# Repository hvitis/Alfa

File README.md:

[English](README.en.md) · **Polski**

# α Alfa

**Małe radio. Wielka wyobraźnia.**

Pastelowa chmurka, sześć przycisków arcade i 32 polskie litery do odkrycia. Alfa odtwarza muzykę i lekcje liter bez sieci.
Wydrukuj obudowę w swoich kolorach, zamontuj elektronikę i stwórz własne radio.

[Prezentacja w przeglądarce](https://hvitis.github.io/Alfa/) · [Najnowszy pakiet](https://github.com/hvitis/Alfa/releases/latest) · [Instrukcja sprzętu](docs/hardware-guide.md) · [Dokumentacja](docs/README.md)

## Zajrzyj do środka

| Połączenia układu | Wnętrze obudowy od tyłu | Widok rentgenowski elementów |
| --- | --- | --- |
|  |  |  |
| [Interaktywny schemat połączeń](https://hvitis.github.io/Alfa/#hardware) | [Wnętrze i montaż chmurki](design/cloud-radio/README.md) | [Pliki do druku chmurki](design/cloud-radio/README.md) |

**Odkryj warsztat:** [3DPrint](https://hvitis.github.io/Alfa/#3dprint) · [Sklejka](https://hvitis.github.io/Alfa/#plywood) · [Elektronika](https://hvitis.github.io/Alfa/#hardware) · [Oprogramowanie](https://hvitis.github.io/Alfa/#software)

**[Raspi 3 PCB — otwórz interaktywny model shielda](https://hvitis.github.io/Alfa/pcb/)** · [Projekt i instrukcja wykonania](design/pi3-shield/README.md).
Prototyp 65 × 56 mm mieści ADC, wzmacniacz i dzielnik bez osobnych modułów. Próby na sprzęcie pozostają do wykonania.

<details open>
<summary>Zobacz warsztat i schemat oprogramowania</summary>

</details>

Folder [CAD](design/) zawiera źródła obudów. Ilustrowany PDF dokumentu ADR jest w zakładce **Software → Design**.

## Specyfikacja

<!-- specifications:start -->
| Specification | Value |
| --- | --- |
| Code and documentation license | MIT |
| Runtime | Python 3.11+ |
| Validation toolchain | Python 3.12, Node.js 22, Chromium |
| Active controller | Raspberry Pi 3, Raspberry Pi OS Bookworm or newer |
| Display | ST7789, 240 × 320, SPI |
| Audio | MAX98357A, I²S, 48 kHz stereo PCM |
| Button input | Five-button keypad, ADS1115 or ADS1015, I²C |
| Divider | 2 × 10 kΩ |
| Backlight | BCM GPIO24 |
| Polish alphabet | 32 letters |
| Initial volume / cap | 20% / 50% |
| Static showcase | HTML, CSS, JavaScript; no backend |
<!-- specifications:end -->

Tabela używa tych samych nazw co wersja angielska, aby automatycznie wykrywać różnice między dokumentami.

## Funkcje

- <!-- feature:offline-player --> **Odtwarzacz bez sieci:** Pięć przycisków służy do zmiany obrazów, odtwarzania nagrań i regulacji głośności.
- <!-- feature:letter-lessons --> **Nauka liter:** Animacja rysuje 32 polskie litery, kreska po kresce. Istniejące grafiki postaci mają osobne informacje o prawach.
- <!-- feature:hardware-simulation --> **Symulacja sprzętu:** Komputer zapisuje podgląd ekranu bez urządzeń GPIO, SPI i I²C.
- <!-- feature:static-showcase --> **Prezentacja statyczna:** Zakładki Plywood, 3DPrint, Hardware i Software zawierają modele 3D, połączenia kontrolerów, ilustrowany PDF ADR i diagram Mermaid.
- <!-- feature:verified-distribution --> **Sprawdzany pakiet:** Pakiet zawiera neutralny obraz demonstracyjny, sumy kontrolne, raporty walidacji i zestawienie elektroniki.
- <!-- feature:enclosure-research --> **Projekty obudów:** Prezentacja obejmuje drukowaną chmurkę i oba projekty ze sklejki. Chmurka ma 206 × 211 × 72 mm, boczną pokrywę baterii, baterię i Pi równoległe do tyłu oraz przyciski zamocowane w przedniej skorupie. Otwory głośnika mają kształt chmur. Pliki STL, 3MF, BREP i kupony pasowania są dołączone; skorupa z brimem 2 mm mieści się w polu Endera 220 × 220 mm. [Opis konstrukcji](design/cloud-radio/README.md) · [30 usprawnień](design/cloud-radio/IMPROVEMENTS.md).

## Szybki start

Użyj Pythona 3.11 lub nowszego. Zainstaluj FFmpeg do konwersji dźwięku.

```bash
python3 -m venv .venv
source .venv/bin/activate
python -m pip install -r requirements/base.txt
python -m app --simulate player --once --no-audio
```

Symulator zapisuje `.state/preview/current.png`. Repozytorium korzysta z istniejących przygotowanych multimediów.
Aplikacja, usługa Pi, ekran startowy i podgląd w przeglądarce używają jednego [config.json](config.json), z wyborem liter w `lesson.letters`.
Plik [installation.md](docs/installation.md) opisuje instalację lokalną i na Pi, a [configuration.md](docs/configuration.md) opisuje ustawienia.
Pakiet wydania zawiera neutralny obraz demonstracyjny.
Połączenia, kalibrację przycisków, sprawdzanie głośnika i instalację usługi opisuje [instrukcja sprzętu](docs/hardware-guide.md).

Po zamontowaniu lub obróceniu przycisków w obudowie uruchom na Pi `make mapping`.
Przypisz kolejno LEWO, PRAWO, GÓRĘ, DÓŁ i ŚRODEK zgodnie z instrukcjami. Polecenie przywraca wcześniej uruchomioną usługę.

Aby wyświetlić obraz na Pi 3 przed uruchomieniem Linuksa, użyj [instrukcji ekranu startowego firmware](docs/early-boot-splash.md).
Opisuje zgodny firmware, `make firmware-splash-install`, kopie zapasowe i usuwanie zmian.

Zainstaluj narzędzia programistyczne i uruchom lokalną prezentację:

```bash
make install
make check
make serve
```

Otwórz lokalny adres wypisany przez `make serve`. System wybiera wolny port; opcjonalnie ustaw `make serve SERVE_PORT=53173`. Testy przeglądarki wymagają Node.js 22.
Plik [build-guide.md](docs/build-guide.md) opisuje wymagania Linuksa i środowisko.

## Automatyczna walidacja

`make check` sprawdza konfigurację, testy Pythona, składnię JavaScript, dane przeglądarki 3D i zgodność dokumentacji dwujęzycznej.
CI eksportuje prezentację i sprawdza ją w Chromium, w katalogu głównym oraz podkatalogu repozytorium, na ekranie komputera i telefonu.
Testy obejmują oba modele ze sklejki, drukowaną obudowę chmurki, połączenia obu kontrolerów, ADR, diagram Mermaid i lokalne zasoby.
`make build` uruchamia również symulator z pakietu i sprawdza zawartość archiwum oraz sumy SHA-256.

Połączenia fizyczne, głośność akustyczna, dopasowanie obudowy i prawa do multimediów wymagają osobnego przeglądu.
Automatyzacja oprogramowania nie potwierdza tych właściwości.

## Budowanie i publikacja

```bash
make smoke
make build
```

Pakiet powstaje jako `output/Alfa-Build-Kit.zip`. Raporty trafiają do `output/reports/`.
Pakiet zawiera aplikację Python, instrukcję połączeń, neutralny obraz i prezentację statyczną z siatkami modeli 3D.
Nie zawiera grafik postaci, nagrań ani starszej przeglądarki. Strona zawiera pliki chmurki do druku. Źródła strony i generator są w [web/](web/README.md).
Przeczytaj [zawartość wydania](docs/release-contents.md), [opis automatyzacji](docs/pipeline.md) i [kroki publikacji](docs/publishing.md).

CI sprawdza pull requesty. GitHub Pages wdraża stronę po poprawnych testach na `main`.
Wydanie wymaga tagu SemVer wskazującego rzeczywisty commit z gałęzi `main`.

## Współpraca i licencje

Plik [contributing.md](docs/contributing.md) opisuje pracę nad kodem.
Problemy bezpieczeństwa zgłaszaj zgodnie z [SECURITY.md](SECURITY.md).
[Licencja MIT](LICENSE) obejmuje oryginalny kod i dokumentację techniczną.
Plik [Informacje o zasobach i zależnościach](docs/third-party-notices.md) opisuje wyłączenia dotyczące zasobów i informacje o zależnościach.

Obudowa jest prototypem do sprawdzenia dopasowania. Próby fizyczne języków ustalających, zatrzasków, upadków i temperatury są nadal wymagane.
Grafiki postaci i nagrania wymagają osobnego przeglądu praw przed publikacją. Zobacz [listę czynności przed publikacją](docs/publishing.md).
Obrazy w README i karty społecznościowe są oryginalnymi renderami CAD.

Aby odtworzyć obrazy, uruchom `make dev`, a potem `npm run render:assets`. Polecenie `make site` eksportuje ilustrowany PDF ADR.
Karta GitHub: [.github/social-preview.png](.github/social-preview.png).

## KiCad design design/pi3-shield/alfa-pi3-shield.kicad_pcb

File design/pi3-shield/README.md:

# Alfa Raspberry Pi 3 shield — prototype A

This is an integrated shield for the current Raspberry Pi 3 Model B application.
The shield replaces the ADC breakout, amplifier breakout, divider perfboard, and their jumper wires.
The LCD, five-button keypad, speaker, power bank, and Raspberry Pi remain separate parts.
Three short cables connect the LCD, keypad, and speaker to the shield.

**Status: engineering prototype for review and quotation. Physical hardware tests are pending.**
The 3D view shows the actual PCB export, with a simplified Pi and underside socket.
Open `http://127.0.0.1:8000/#hardware` and select **Raspi 3 PCB**, the third controller option.

## Board and assembly

| Item | Specification |
|---|---|
| Outline | 65 × 56 mm, 3 mm corner radii |
| PCB | Two copper layers, FR-4, 1.6 mm, proposed 35 µm copper |
| Mounting | Four 2.75 mm unplated holes, 58 × 49 mm centers, M2.5 hardware |
| Raspberry Pi connection | J1, 40-pin female socket on the **underside** |
| Factory SMT assembly | U1/U2, R1–R4, C1–C4, all on the top |
| Through-hole assembly | J1 underside, J2/J3/J4 top; request hand assembly from the supplier |
| Power | Existing Pi micro-USB input only; the shield draws 5 V and 3.3 V through J1 |
| Board identification | No EEPROM; this is an add-on shield, not a complete HAT implementation |

The proposed socket is Samtec **SSQ-120-01-G-D**, with 2.64 mm solder tails.
The socket body is approximately 8.51 mm high.
The preview uses an approximately 11 mm gap between the Pi top and shield underside.
The final socket engagement and spacer length require a physical fit check.
The socket, standoffs, and Pi header must fit without bending either board.
The Pi USB and Ethernet housings extend beyond the shield's right edge.
Camera and DSI cable cutouts are omitted because this application does not use those interfaces.

## Integrated circuits

**U1: ADS1115IDGSR**, VSSOP-10, runs from 3.3 V.
ADDR connects to ground for address `0x48`. The keypad uses AIN0.
Unused analog inputs connect to ground. ALERT/RDY remains unconnected.
The Pi supplies the I²C pull-ups. The shield adds no parallel pull-ups.
The selected part matches the repository's `ads1115` configuration.

**U2: MAX98357AETE+T**, 16-pin TQFN with exposed pad, runs from 5 V.
The **A** variant accepts the existing I²S stream.
GAIN_SLOT remains unconnected for 9 dB gain.
GPIO23 reaches SD_MODE through R3, a 1 kΩ resistor.
R4, 100 kΩ to ground, keeps the amplifier off until GPIO23 rises.
A high level selects the left audio channel, as the current application expects.
This circuit has no 5 V pull-up on the GPIO control signal.

R1 and R2 are 10 kΩ, 1% parts.
They divide a nominal 5 V keypad output to approximately 2.5 V at AIN0.
The keypad's internal resistors affect the actual levels, so final calibration remains necessary.
C1 decouples the ADC. C2/C3 decouple the amplifier, and C4 provides local supply capacitance.
The ceramic capacitors lose capacitance under DC bias. Hardware tests must cover supply dips during loud audio.

## Connectors and cables

The PCB connectors are keyed **JST PH, 2.00 mm pitch**.
They do not directly accept existing 2.54 mm Dupont sockets.
An assembler can supply the three harnesses, with loose or soldered ends for the existing modules.
The numbers in the assembly drawings identify pin 1. The connector latch defines mating orientation.

| Connector | Pins, in numerical order | Matching housing |
|---|---|---|
| J2 LCD | 1=3V3, 2=GND, 3=DIN, 4=CLK, 5=CS, 6=DC, 7=RST, 8=BL | PHR-8 |
| J3 speaker | 1=SPK+, 2=SPK− | PHR-2 |
| J4 keypad | 1=OUT, 2=5V, 3=GND | PHR-3 |

JST **SPH-002T-P0.5S** contacts suit the proposed PH housings and appropriate small-gauge wires.
Use the manufacturer's wire and crimp specifications when selecting the harness wire.
The LCD cable must map to the module's printed labels. Its existing connector order is not assumed.
The existing keypad order is OUT, VCC, GND, as recorded in the repository photos.
Neither speaker terminal connects to ground.
The 5 V keypad signal reaches the ADC only through R1/R2.

## Existing Pi software

The shield keeps these physical header assignments:

| Function | Physical Pi pin | BCM GPIO |
|---|---:|---:|
| ADC SDA / SCL | 3 / 5 | 2 / 3 |
| Audio BCLK / LRCLK / DIN | 12 / 35 / 40 | 18 / 19 / 21 |
| Amplifier enable | 16 | 23 |
| LCD DIN / CLK / CS | 19 / 23 / 24 | 10 / 11 / 8 |
| LCD DC / RESET / backlight | 22 / 13 / 18 | 25 / 27 / 24 |

The current `config.json` already matches these assignments.
The existing `dtoverlay=max98357a,no-sdmode` setting remains applicable.
The Python app controls amplifier sleep through GPIO23.
The earlier wiring table leaves the breakout SD pin open. The later sleep section adds GPIO23.
This shield implements the later sleep circuit directly.

## Files for a manufacturer

Run `make pcb` from the repository root. The generated files are in `design/pi3-shield/generated/`.
The editable KiCad project, local libraries, and package STEP models remain in this source folder.

- `alfa-pi3-shield.kicad_pro`, `.kicad_sch`, `.kicad_pcb`: editable KiCad 9 project.
- `Alfa.kicad_sym`, `Alfa.pretty`, and library tables: local symbols and underside socket footprint.
- `generated/fabrication-draft.zip`: Gerber layers, board outline, plated and unplated Excellon drills, and drill maps.
- `bom.csv`: manufacturer part numbers and assembly sides.
- `placement.csv`: **SMT parts only**, millimeters, origin at the PCB lower-left corner, positive Y upward.
- `assembly-top.pdf`, `assembly-bottom.pdf`: assembly reference and connector orientation.
- `schematic.pdf`: electrical design.
- `shield.step`, `shield.glb`: mechanical and browser models.
- `erc.rpt`, `drc.rpt`, `verification.json`: digital check results.

The placement origin is `(100,156)` in the KiCad editor's absolute coordinates.
The Gerbers, drill files, and placement file use this same lower-left origin.
The assembler must review rotations against the component pin-1 marks.
Through-hole connectors require the drawings and BOM rather than the SMT placement file.
The BOM proposes exact parts. Supplier availability and substitutions require review during quotation.

The amplifier exposed pad connects to ground through a 0.3 mm thermal via.
Ask the assembler to review solder-paste coverage and via wicking for the exposed pad.
The board has no battery charger, external power input, or added power switching.
The existing power bank and inline switch continue to supply the Pi.

## Physical checks before ordering a batch

1. Print the assembly drawing at actual size.
2. Compare the shield holes and header against the real Pi 3.
3. Select the socket and matching M2.5 spacers.
4. Check connector height, cable bends, enclosure clearance, and access to the Pi ports.
5. Ask the assembler to review IC packages, pin orientation, exposed-pad soldering, and harness pin order.
6. Order a small prototype batch.

## First hardware test

1. Keep the shield disconnected from the Pi during the initial resistance inspection.
2. Check for shorts between 5 V, 3.3 V, and ground.
3. Check the three harnesses against the connector table.
4. Connect the shield with the Pi power disconnected.
5. Supply power through the Pi micro-USB input.
6. Check TP1 for 5 V and TP2 for 3.3 V, relative to TP3 ground.
7. Run the repository's hardware checks and LCD test.
8. Check ADC address `0x48` and calibrate every keypad button.
9. Play audio at low volume before increasing it to the existing application limit.
10. Check supply voltage, Pi undervoltage reports, amplifier temperature, and Pi temperature during combined display and audio operation.
11. Check GPIO23 sleep, wake, repeated cold starts, and the physical switch.

No physical fit, electrical, acoustic, thermal, or enclosure test is complete at this revision.
Digital checks establish connectivity and layout constraints. They do not establish hardware performance.

## Refresh before staging

Run `make prepare-commit` from the repository root.
This command regenerates PCB exports, rebuilds the static website, and checks the export hashes.
It does not stage, commit, or stash any files.
The generated manufacturing files and website models are ignored by Git.

`make pcb` refreshes only the PCB exports. It requires a running Docker daemon.
`make pcb-check` checks the source and output hashes without Docker or KiCad.
`make site` and `make dev` regenerate missing or stale PCB exports before loading the website.
They never silently reuse an export after its PCB source changes.

GitHub Actions can generate these files on its Linux runner.
The reusable `pcb.yml` workflow runs the same pinned container and uploads all exports as an artifact.
The website and release workflows download that artifact from the same commit before building.
The workflow retains the editable routed PCB. It does not autoroute the circuit during each publication.
The two package STEP files are source assets, like the footprint libraries.
FreeCAD is only needed when changing those package models.

## Rebuild the circuit layout

The files were generated with KiCad **9.0.9**, Freerouting **1.9.0**, and FreeCAD.
The KiCad image is `kicad/kicad:9.0-full`, digest `sha256:f7d67c2bfff3733b84d5ef9b47eff152a69c1cd7ac1f8060bcc1d98a857a8913`.
The image uses x86-64 emulation on Apple Silicon.

1. Run `python3 build.py` with KiCad's `pcbnew` module available.
2. Route `alfa-pi3-shield.dsn` with Freerouting and save `alfa-pi3-shield.ses`.
3. Run `python3 build.py --finish`.
4. Run `build_models.py` with FreeCAD's Python interpreter and library path.
5. Run `make pcb` from the repository root to export and check the finished design.

The normal export command never modifies the editable source files.
It runs KiCad on temporary copies and publishes the generated snapshot only after the checks pass.
The source and output SHA-256 hashes are stored in `generated/manifest.json`.
The website rejects changed, missing, or mixed snapshots.

For example, mount this folder at `/work` in the pinned KiCad image.
Use `docker run --rm --platform linux/amd64 -v "$PWD:/work" -w /work --entrypoint python3 kicad/kicad:9.0-full build.py`.
Freerouting accepts `-de alfa-pi3-shield.dsn -do alfa-pi3-shield.ses -mp 40 -mt 1 -da -dct 0`.
The router completes signal connections. The generator preserves the fine-pitch amplifier escapes and repairs the adjacent VDD connection.

## Sources

- Repository: `docs/wiring.md`, its amplifier sleep section, `config.json`, and the measured component records.
- [Raspberry Pi add-on board mechanical drawing](https://github.com/raspberrypi/hats/blob/master/hat-board-mechanical.pdf).
- [Raspberry Pi add-on board design guide](https://github.com/raspberrypi/hats/blob/master/designguide.md).
- [Raspberry Pi 3 Model B mechanical drawing](https://datasheets.raspberrypi.com/rpi3/raspberry-pi-3-b-mechanical-drawing.pdf).
- [TI ADS1115 datasheet, DGS package and pin functions](https://www.ti.com/lit/ds/symlink/ads1115.pdf).
- [Analog Devices MAX98357A datasheet, TQFN pin functions and supply layout](https://www.analog.com/media/en/technical-documentation/data-sheets/max98357a-max98357b.pdf).
- [Samtec SSQ-120-01-G-D socket](https://www.samtec.com/products/ssq-120-01-g-d).

Standard footprints and most package models come from KiCad's installed libraries.
The ADS1115 and MAX98357A STEP models are package envelopes generated by `build_models.py`.

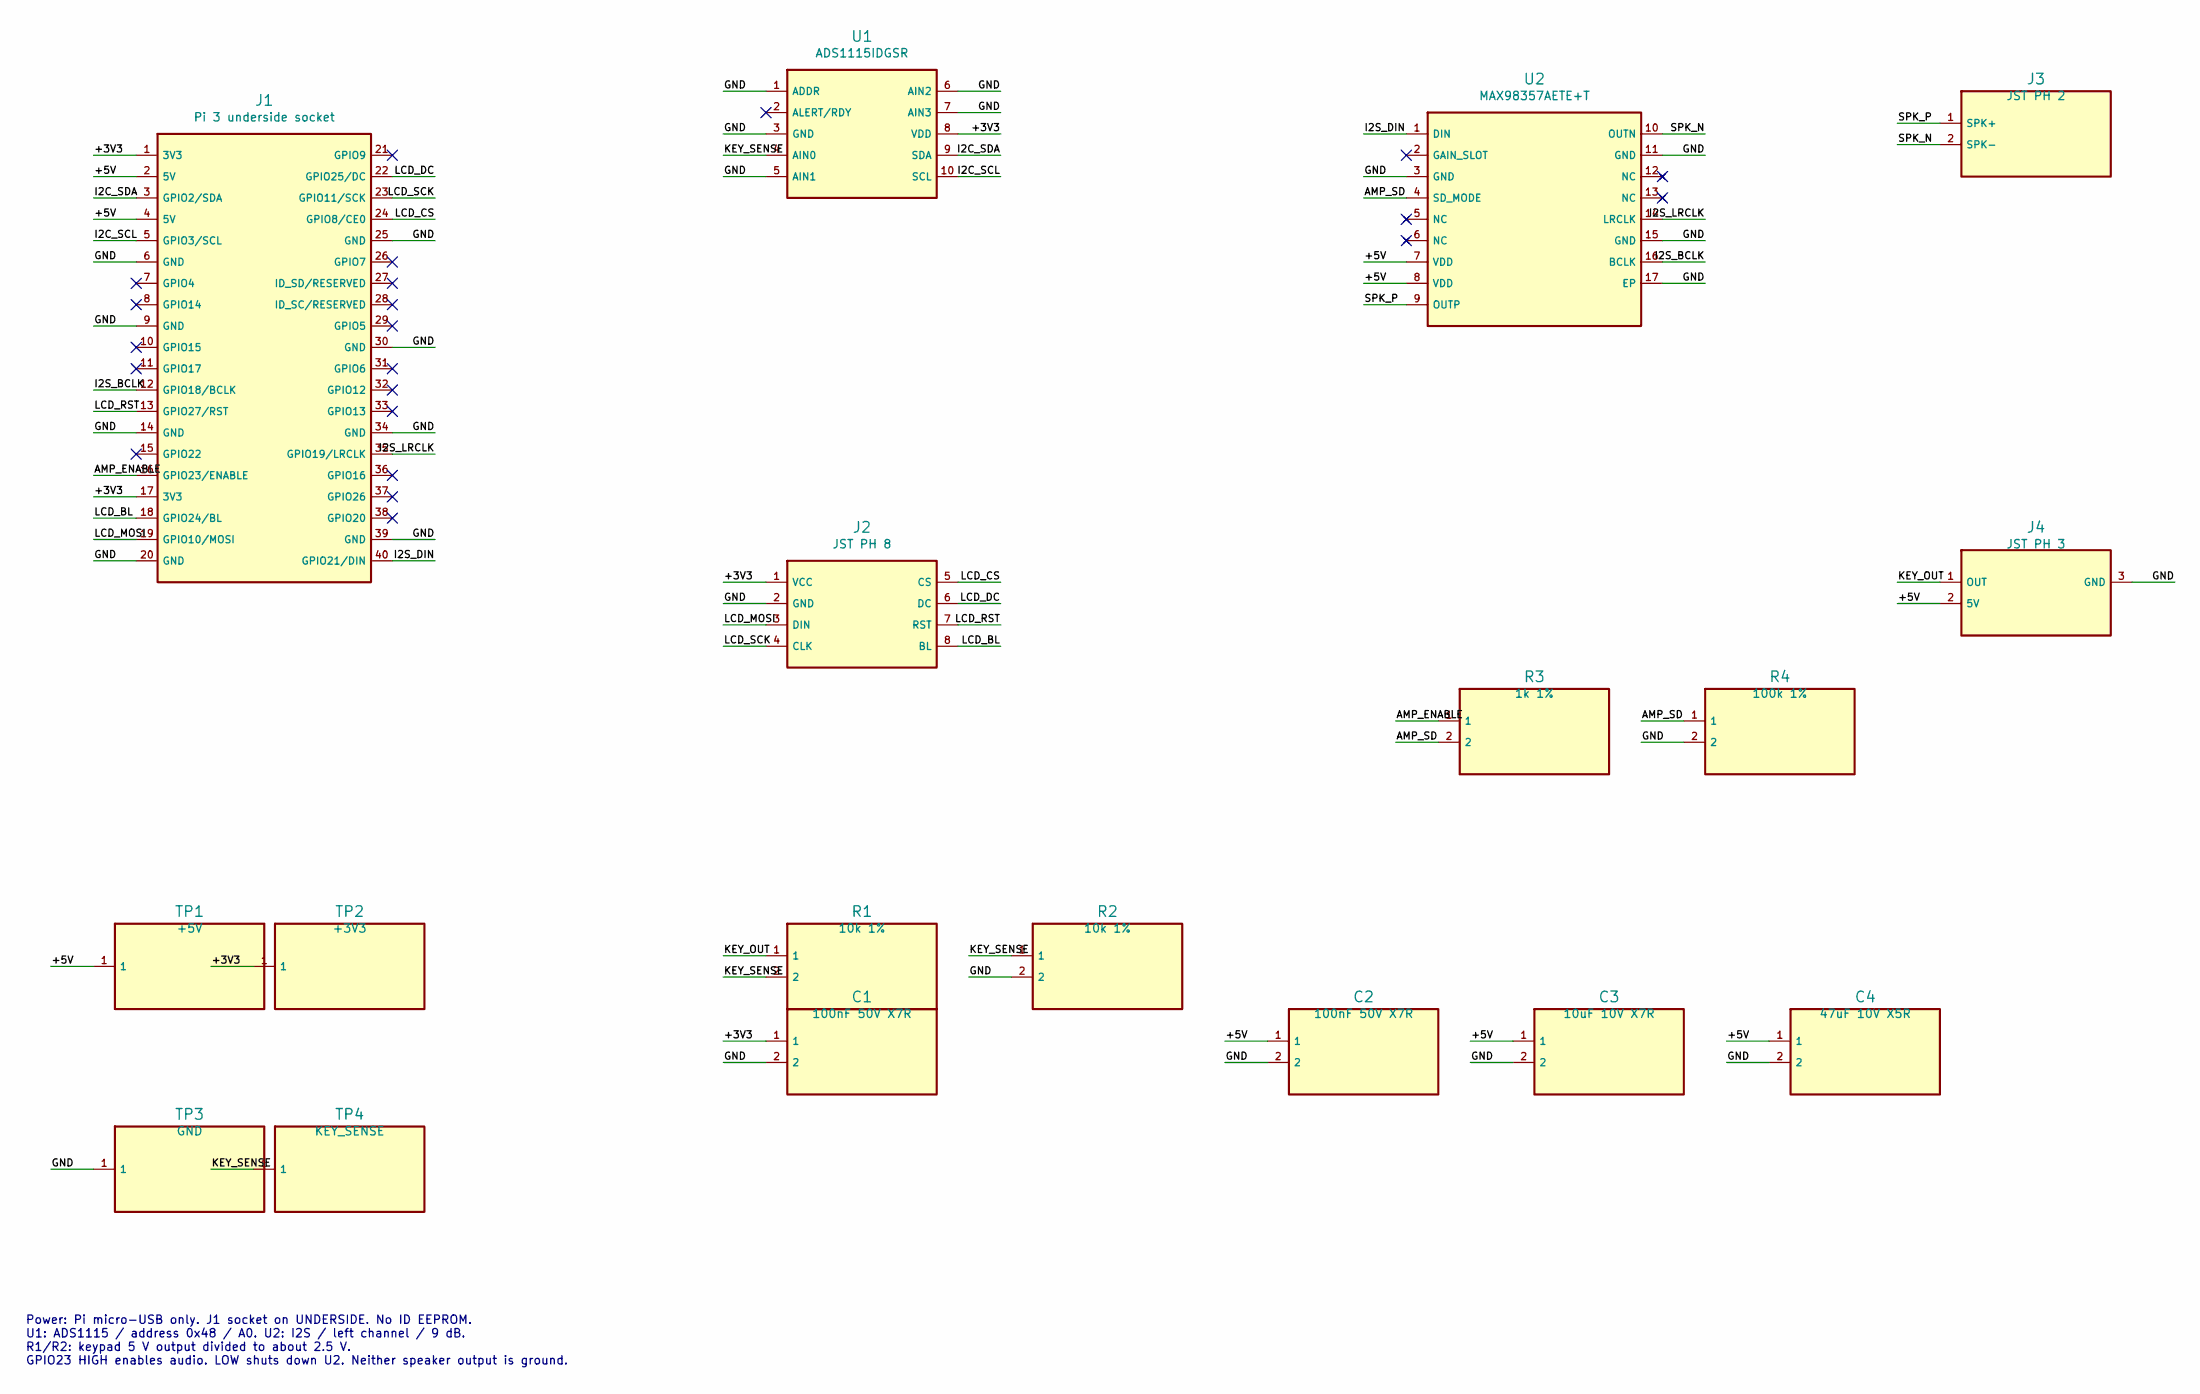
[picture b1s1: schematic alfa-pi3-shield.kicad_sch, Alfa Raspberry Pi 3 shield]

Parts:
C1, C2: 100nF 50V X7R; C_0805_2012Metric; MPN GRM21BR71H104KA01L
C3: 10uF 10V X7R; C_1206_3216Metric; MPN GRM31CR71A106KA01L
C4: 47uF 10V X5R; C_1210_3225Metric; MPN GRM32ER61A476KE20L
J1: Pi 3 underside socket; Pi_40_Underside; MPN SSQ-120-01-G-D
J2: JST PH 8; JST_PH_B8B-PH-K_1x08_P2.00mm_Vertical; MPN B8B-PH-K-S(LF)(SN)
J3: JST PH 2; JST_PH_B2B-PH-K_1x02_P2.00mm_Vertical; MPN B2B-PH-K-S(LF)(SN)
J4: JST PH 3; JST_PH_B3B-PH-K_1x03_P2.00mm_Vertical; MPN B3B-PH-K-S(LF)(SN)
R1, R2: 10k 1%; R_0805_2012Metric; MPN RC0805FR-0710KL
R3: 1k 1%; R_0805_2012Metric; MPN RC0805FR-071KL
R4: 100k 1%; R_0805_2012Metric; MPN RC0805FR-07100KL
TP1: +5V; TestPoint_Pad_D1.5mm
TP2: +3V3; TestPoint_Pad_D1.5mm
TP3: GND; TestPoint_Pad_D1.5mm
TP4: KEY_SENSE; TestPoint_Pad_D1.5mm
U1: ADS1115IDGSR; VSSOP-10_3x3mm_P0.5mm; MPN ADS1115IDGSR
U2: MAX98357AETE+T; TQFN-16-1EP_3x3mm_P0.5mm_EP1.23x1.23mm; MPN MAX98357AETE+T

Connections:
+3V3: C1.1, J1.1 (3V3), J1.17 (3V3), J2.1 (VCC), TP2.1, U1.8 (VDD)
+5V: C2.1, C3.1, C4.1, J1.2 (5V), J1.4 (5V), J4.2 (5V), TP1.1, U2.7 (VDD), U2.8 (VDD)
AMP_ENABLE: J1.16 (GPIO23/ENABLE), R3.1
AMP_SD: R3.2, R4.1, U2.4 (SD_MODE)
GND: C1.2, C2.2, C3.2, C4.2, J1.6 (GND), J1.9 (GND), J1.14 (GND), J1.20 (GND), J1.25 (GND), J1.30 (GND), J1.34 (GND), J1.39 (GND), J2.2 (GND), J4.3 (GND), R2.2, R4.2, TP3.1, U1.1 (ADDR), U1.3 (GND), U1.5 (AIN1), U1.6 (AIN2), U1.7 (AIN3), U2.3 (GND), U2.11 (GND), U2.15 (GND), U2.17 (EP)
I2C_SCL: J1.5 (GPIO3/SCL), U1.10 (SCL)
I2C_SDA: J1.3 (GPIO2/SDA), U1.9 (SDA)
I2S_BCLK: J1.12 (GPIO18/BCLK), U2.16 (BCLK)
I2S_DIN: J1.40 (GPIO21/DIN), U2.1 (DIN)
I2S_LRCLK: J1.35 (GPIO19/LRCLK), U2.14 (LRCLK)
KEY_OUT: J4.1 (OUT), R1.1
KEY_SENSE: R1.2, R2.1, TP4.1, U1.4 (AIN0)
LCD_BL: J1.18 (GPIO24/BL), J2.8 (BL)
LCD_CS: J1.24 (GPIO8/CE0), J2.5 (CS)
LCD_DC: J1.22 (GPIO25/DC), J2.6 (DC)
LCD_MOSI: J1.19 (GPIO10/MOSI), J2.3 (DIN)
LCD_RST: J1.13 (GPIO27/RST), J2.7 (RST)
LCD_SCK: J1.23 (GPIO11/SCK), J2.4 (CLK)
SPK_N: J3.2 (SPK-), U2.10 (OUTN)
SPK_P: J3.1 (SPK+), U2.9 (OUTP)

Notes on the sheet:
Power: Pi micro-USB only. J1 socket on UNDERSIDE. No ID EEPROM. U1: ADS1115 / address 0x48 / A0. U2: I2S / left channel / 9 dB. R1/R2: keypad 5 V output divided to about 2.5 V. GPIO23 HIGH enables audio. LOW shuts down U2. Neither speaker output is ground.

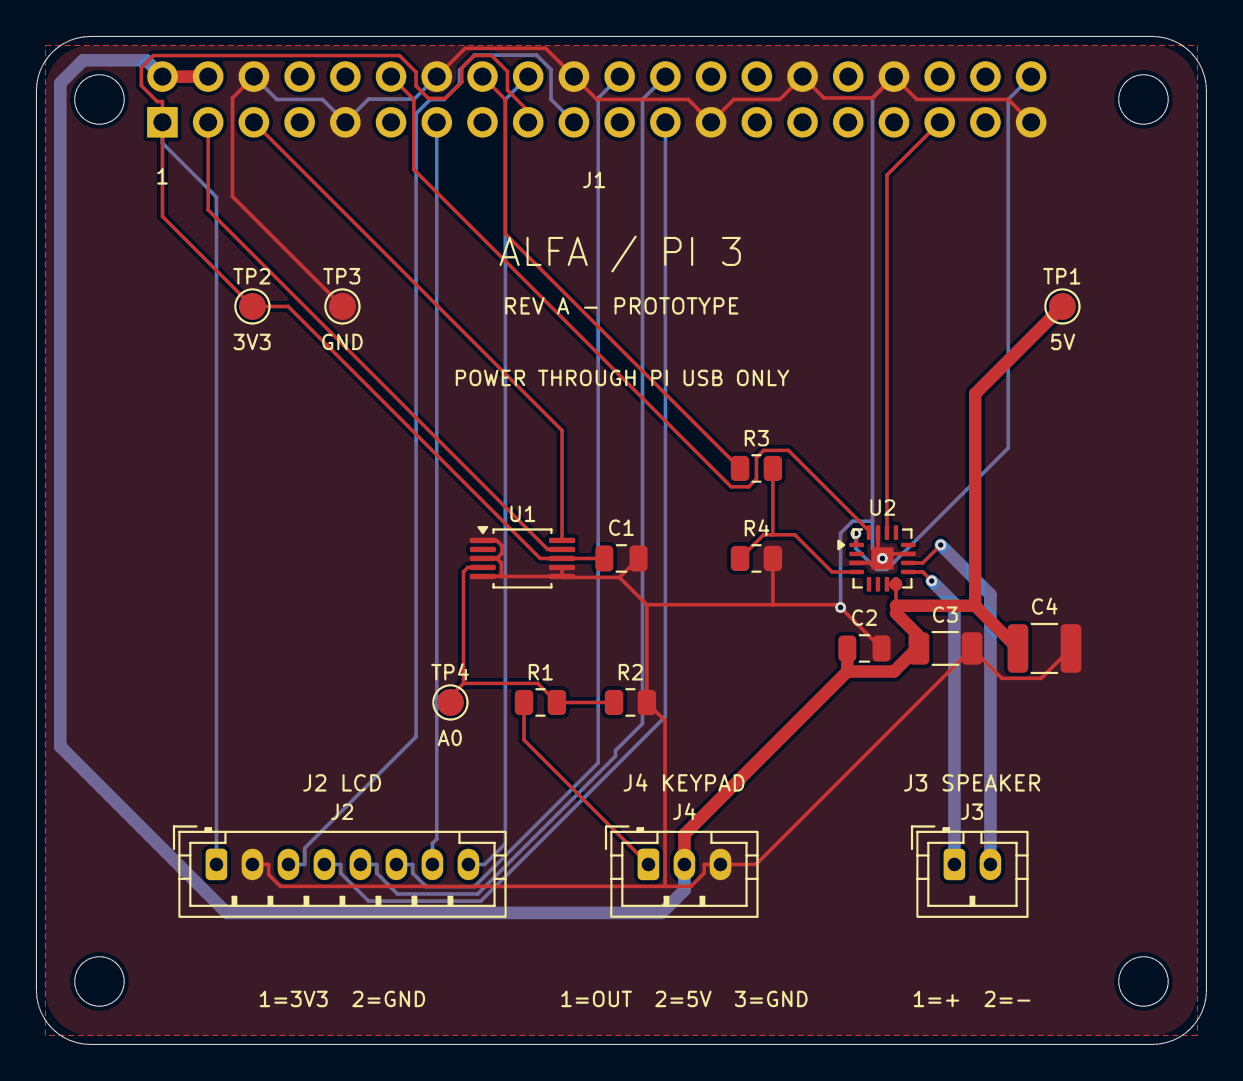
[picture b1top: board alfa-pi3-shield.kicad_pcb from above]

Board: 2 copper layers, 65.0 x 56.0 mm, 22 parts (1 on the bottom side), 20 nets.

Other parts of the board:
H1, H2, H3, H4: MountingHole_2.7mm_M2.5

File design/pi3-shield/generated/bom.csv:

Reference,Quantity,Value,Manufacturer,MPN,Footprint,Assembly,Notes
J1,1,Pi 3 underside socket,Samtec,SSQ-120-01-G-D,Alfa:Pi_40_Underside,THT underside,"2x20 female, 2.54 mm; select socket/standoff heights as a matched pair."
U1,1,ADS1115IDGSR,Texas Instruments,ADS1115IDGSR,Package_SO:VSSOP-10_3x3mm_P0.5mm,SMT top,16-bit ADC; address 0x48; A0 keypad input. Replaces ADS breakout.
U2,1,MAX98357AETE+T,Analog Devices,MAX98357AETE+T,Package_DFN_QFN:TQFN-16-1EP_3x3mm_P0.5mm_EP1.23x1.23mm,SMT top,"I2S A variant, 16-pin TQFN, gain pin open = 9 dB; left channel."
J2,1,JST PH 8,JST,B8B-PH-K-S(LF)(SN),Connector_JST:JST_PH_B8B-PH-K_1x08_P2.00mm_Vertical,THT top,Through-hole; supplier can hand-assemble. Harness pin order is defined by this PCB.
J3,1,JST PH 2,JST,B2B-PH-K-S(LF)(SN),Connector_JST:JST_PH_B2B-PH-K_1x02_P2.00mm_Vertical,THT top,Through-hole; supplier can hand-assemble. Harness pin order is defined by this PCB.
J4,1,JST PH 3,JST,B3B-PH-K-S(LF)(SN),Connector_JST:JST_PH_B3B-PH-K_1x03_P2.00mm_Vertical,THT top,Through-hole; supplier can hand-assemble. Harness pin order is defined by this PCB.
R1,1,10k 1%,Yageo,RC0805FR-0710KL,Resistor_SMD:R_0805_2012Metric,SMT top,
R2,1,10k 1%,Yageo,RC0805FR-0710KL,Resistor_SMD:R_0805_2012Metric,SMT top,
R3,1,1k 1%,Yageo,RC0805FR-071KL,Resistor_SMD:R_0805_2012Metric,SMT top,
R4,1,100k 1%,Yageo,RC0805FR-07100KL,Resistor_SMD:R_0805_2012Metric,SMT top,
C1,1,100nF 50V X7R,Murata,GRM21BR71H104KA01L,Capacitor_SMD:C_0805_2012Metric,SMT top,
C2,1,100nF 50V X7R,Murata,GRM21BR71H104KA01L,Capacitor_SMD:C_0805_2012Metric,SMT top,
C3,1,10uF 10V X7R,Murata,GRM31CR71A106KA01L,Capacitor_SMD:C_1206_3216Metric,SMT top,
C4,1,47uF 10V X5R,Murata,GRM32ER61A476KE20L,Capacitor_SMD:C_1210_3225Metric,SMT top,

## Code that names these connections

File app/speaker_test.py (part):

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                report.emit("MODE", "SIMULATION: no GPIO, SPI or ALSA output" if simulate else "Raspberry Pi hardware")
                report.emit("VOLUME", f"{volume:.0%} digital volume; {repeat} playback(s)")
                report.emit("WIRING", "max4 header: LRC, BCLK, DIN, GAIN, SD, GND, VIN", detail=True)
                report.emit("WIRING", "LRC -> physical 35 / GPIO19; BCLK -> physical 12 / GPIO18; DIN -> physical 40 / GPIO21", detail=True)
                report.emit("WIRING", "VIN -> physical 2 / 5 V; GND -> physical 9; speaker +/- -> amplifier +/-; GAIN and SD unwired", detail=True)
                if with_screen:
                    phase = "LCD initialization"
                    report.emit("LCD", "Opening SPI0/CE0. BL uses GPIO24 (physical 18); audio BCLK uses GPIO18 (physical 12).")
                    display = PreviewDisplay(settings) if simulate else ST7789(settings)
                    resources.callback(display.close)
                    show("Preparing audio", ["Speaker is the main test.", f"Volume: {volume:.0%}", "See the SSH log."], name="speaker-start")
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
